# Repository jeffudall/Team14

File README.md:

Welcome to Team 14's Practicum Pages - ECE 411 Fall 2017

This repository will document our practicum project for the ECE 411 Industrial Design course at PSU for Fall 2017. Here you will find details of our project creation as well as documentation detailing the specifications and operation of our final product - a color scanner device.

Team members:

- Matthew Fleetwood fleet@pdx.edu
- Bruce Griffin bruce7@pdx.edu
- Jeffrey Udall judall@pdx.edu
- James Witcher jwitcher@pdx.edu

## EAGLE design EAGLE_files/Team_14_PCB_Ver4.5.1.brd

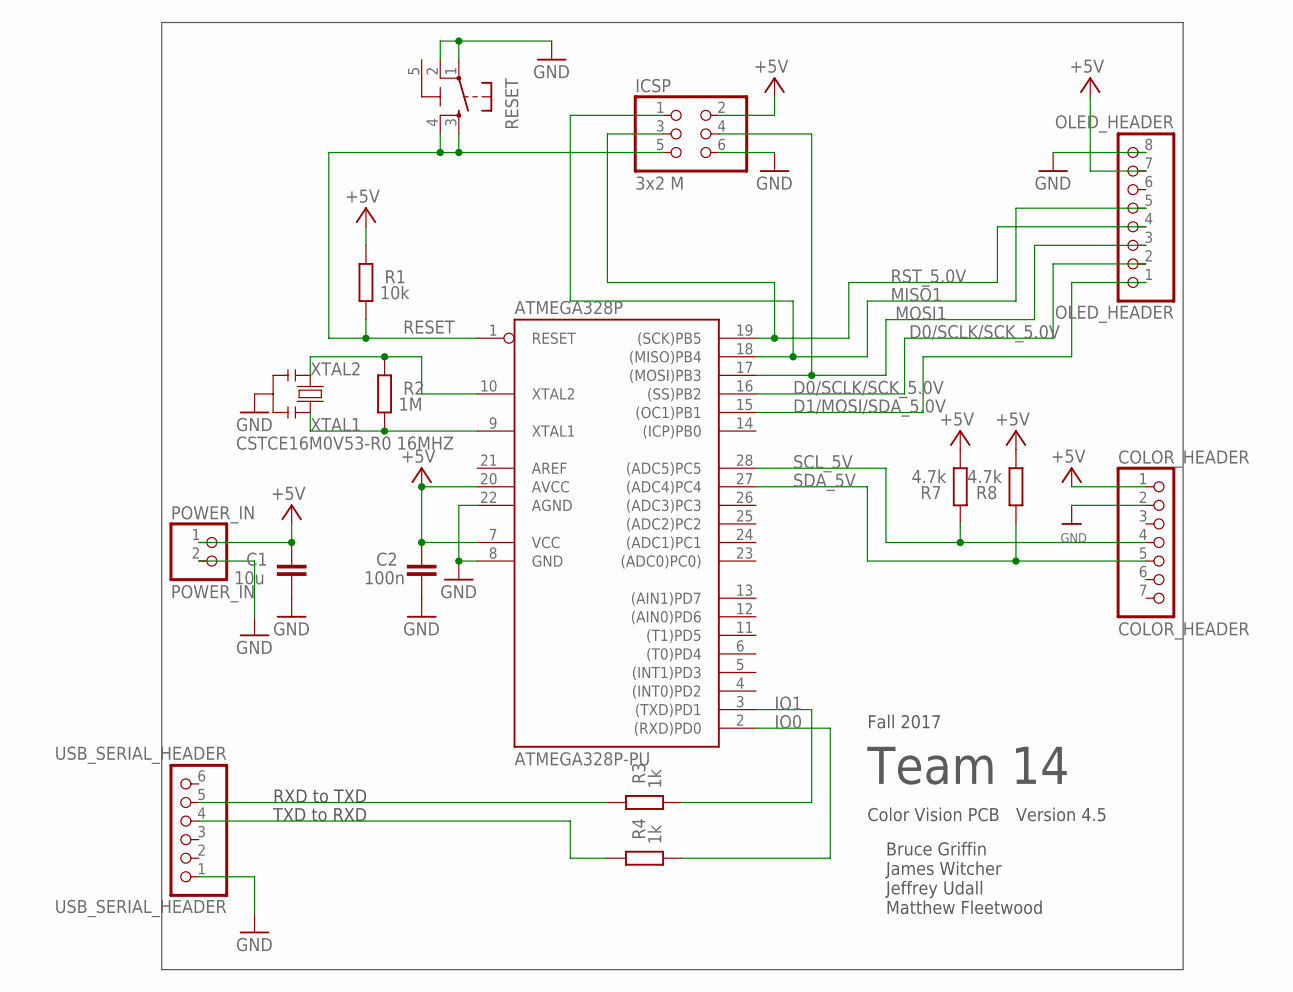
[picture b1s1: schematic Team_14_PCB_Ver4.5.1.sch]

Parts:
ATMEGA328P: ATMEGA328P-PU; DIL28-3
C1: 10u; C0603-ROUND
C2: 100n; C0603-ROUND
COLOR_HEADER: COLOR_HEADER; 1X07_ROUND_70
ICSP: 3x2 M; 2X03
OLED_HEADER: OLED_HEADER; 1X08_ROUND_70
POWER_IN: POWER_IN; 1X02
R1: 10k; R0603-ROUND
R2: 1M; R0603-ROUND
R3, R4: 1k; R0603-ROUND
R7, R8: 4.7k; R0603-ROUND
RESET: TS42
USB_SERIAL_HEADER: USB_SERIAL_HEADER; 1X06
Y2: CSTCE16M0V53-R0 16MHZ; RESONATOR

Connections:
5-GND: RESET.5 (5-GND)
+5V: ATMEGA328P.7 (VCC), ATMEGA328P.20 (AVCC), C1.2, C2.2, COLOR_HEADER.1, ICSP.2, OLED_HEADER.7, POWER_IN.1, R1.2, R7.1, R8.1
D0/SCLK/SCK_5.0V: ATMEGA328P.16 ((SS)PB2), OLED_HEADER.2
D1/MOSI/SDA_5.0V: ATMEGA328P.15 ((OC1)PB1), OLED_HEADER.1
GND: ATMEGA328P.8 (GND), ATMEGA328P.22 (AGND), C1.1, C2.1, COLOR_HEADER.2, ICSP.6, OLED_HEADER.8, POWER_IN.2, RESET.1, RESET.2, USB_SERIAL_HEADER.1, Y2.2
IO0: ATMEGA328P.2 ((RXD)PD0), R4.1
IO1: ATMEGA328P.3 ((TXD)PD1), R3.1
MISO1: ATMEGA328P.18 ((MISO)PB4), ICSP.1, OLED_HEADER.5
MOSI1: ATMEGA328P.17 ((MOSI)PB3), ICSP.4, OLED_HEADER.3
unnamed: R3.2, USB_SERIAL_HEADER.5
unnamed: R4.2, USB_SERIAL_HEADER.4
RESET: ATMEGA328P.1 (RESET), ICSP.5, R1.1, RESET.3, RESET.4
RST_5.0V: ATMEGA328P.19 ((SCK)PB5), ICSP.3, OLED_HEADER.4
SCL_5V: ATMEGA328P.28 ((ADC5)PC5), COLOR_HEADER.4, R7.2
SDA_5V: ATMEGA328P.27 ((ADC4)PC4), COLOR_HEADER.5, R8.2
XTAL1: ATMEGA328P.9 (XTAL1), R2.1, Y2.3
XTAL2: ATMEGA328P.10 (XTAL2), R2.2, Y2.1

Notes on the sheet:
Team 14
Bruce Griffin James Witcher Jeffrey Udall Matthew Fleetwood
Color Vision PCB
Version 4.5
Fall 2017
RXD to TXD
TXD to RXD

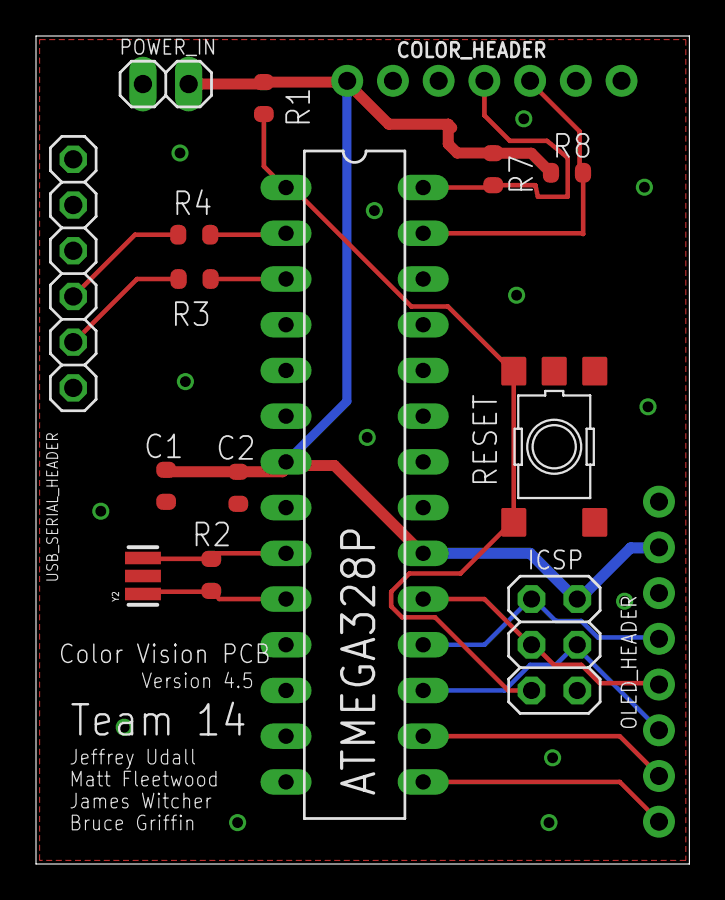
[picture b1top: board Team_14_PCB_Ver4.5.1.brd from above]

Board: 2 copper layers, 36.3 x 46.0 mm, 16 parts (0 on the bottom side), 16 nets.

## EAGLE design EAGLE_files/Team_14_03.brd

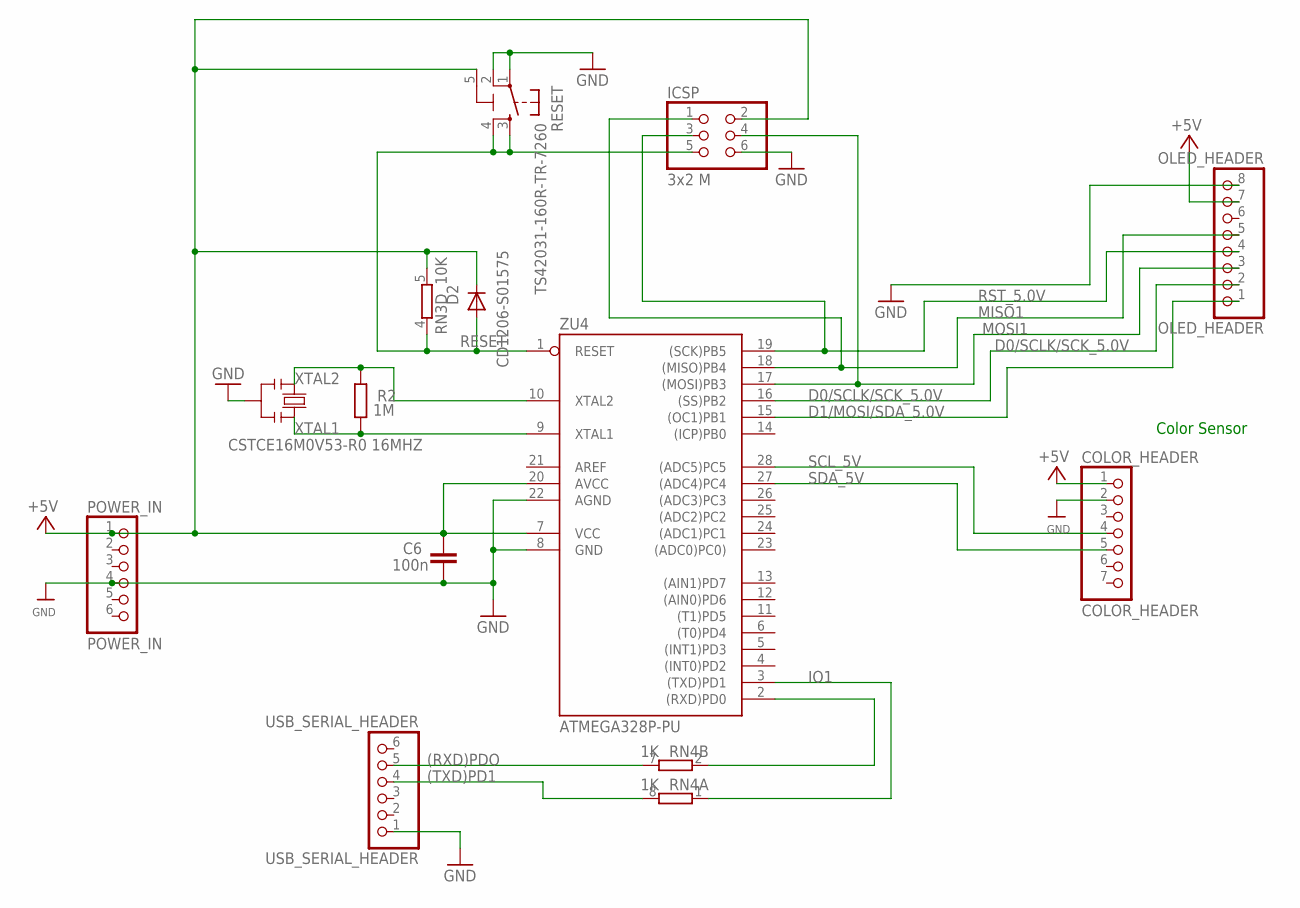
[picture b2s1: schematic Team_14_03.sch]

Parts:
C6: 100n; C0603-ROUND
COLOR_HEADER: COLOR_HEADER; 1X07_ROUND_70
D2: CD1206-S01575; MINIMELF
ICSP: 3x2 M; 2X03
OLED_HEADER: OLED_HEADER; 1X08_ROUND_70
POWER_IN: POWER_IN; 1X06
R2: 1M; R0603-ROUND
RESET: TS42031-160R-TR-7260; TS42
RN3: 10K; CAY16
RN4: 1K; CAY16
USB_SERIAL_HEADER: USB_SERIAL_HEADER; 1X06
Y2: CSTCE16M0V53-R0 16MHZ; RESONATOR
ZU4: ATMEGA328P-PU; DIL28-3

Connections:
(RXD)PDO: RN4.7 (2), USB_SERIAL_HEADER.5
(TXD)PD1: RN4.8 (2), USB_SERIAL_HEADER.4
+5V: C6.2, COLOR_HEADER.1, D2.C, ICSP.2, OLED_HEADER.7, POWER_IN.1, RESET.5 (5-GND), RN3.5 (2), ZU4.7 (VCC), ZU4.20 (AVCC)
D0/SCLK/SCK_5.0V: OLED_HEADER.2, ZU4.16 ((SS)PB2)
D1/MOSI/SDA_5.0V: OLED_HEADER.1, ZU4.15 ((OC1)PB1)
GND: C6.1, COLOR_HEADER.2, ICSP.6, OLED_HEADER.8, POWER_IN.4, RESET.1, RESET.2, USB_SERIAL_HEADER.1, Y2.2, ZU4.8 (GND), ZU4.22 (AGND)
IO1: RN4.1, ZU4.3 ((TXD)PD1)
IO11: RN4.2 (1), ZU4.2 ((RXD)PD0)
MISO1: ICSP.1, OLED_HEADER.5, ZU4.18 ((MISO)PB4)
MOSI1: ICSP.4, OLED_HEADER.3, ZU4.17 ((MOSI)PB3)
RESET: D2.A, ICSP.5, RESET.3, RESET.4, RN3.4 (1), ZU4.1 (RESET)
RST_5.0V: ICSP.3, OLED_HEADER.4, ZU4.19 ((SCK)PB5)
SCL_5V: COLOR_HEADER.4, ZU4.28 ((ADC5)PC5)
SDA_5V: COLOR_HEADER.5, ZU4.27 ((ADC4)PC4)
XTAL1: R2.1, Y2.3, ZU4.9 (XTAL1)
XTAL2: R2.2, Y2.1, ZU4.10 (XTAL2)

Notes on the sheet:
Color Sensor

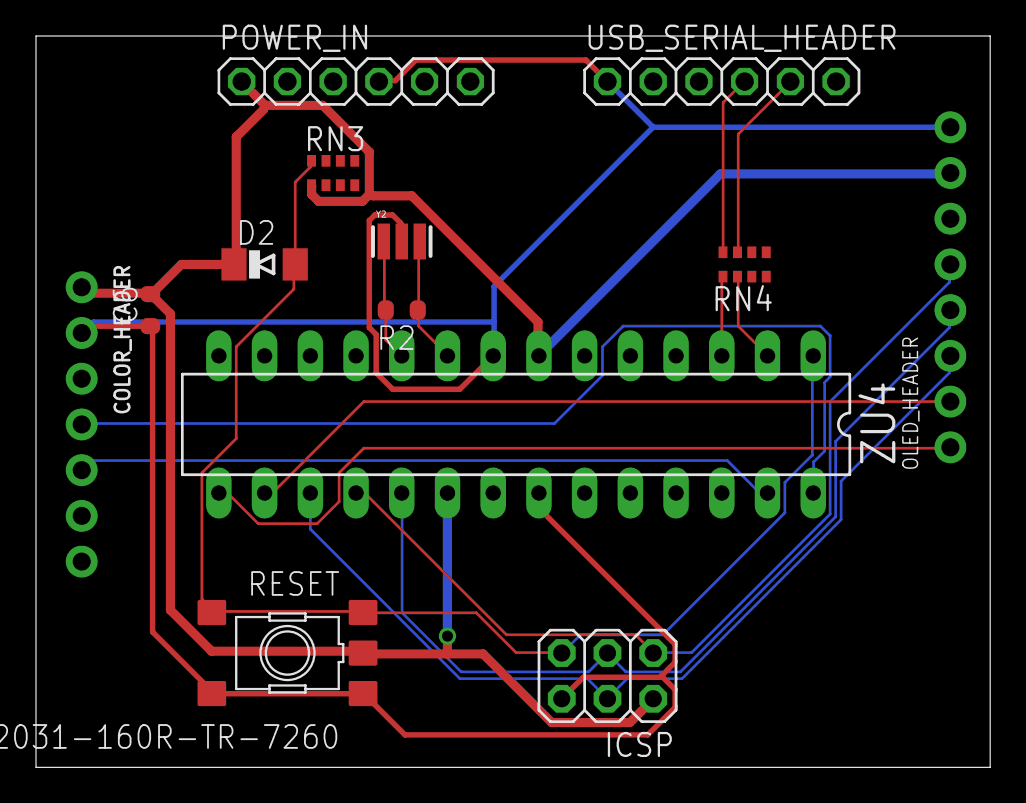
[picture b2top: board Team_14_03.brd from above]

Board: 2 copper layers, 53.0 x 40.6 mm, 13 parts (0 on the bottom side), 16 nets.

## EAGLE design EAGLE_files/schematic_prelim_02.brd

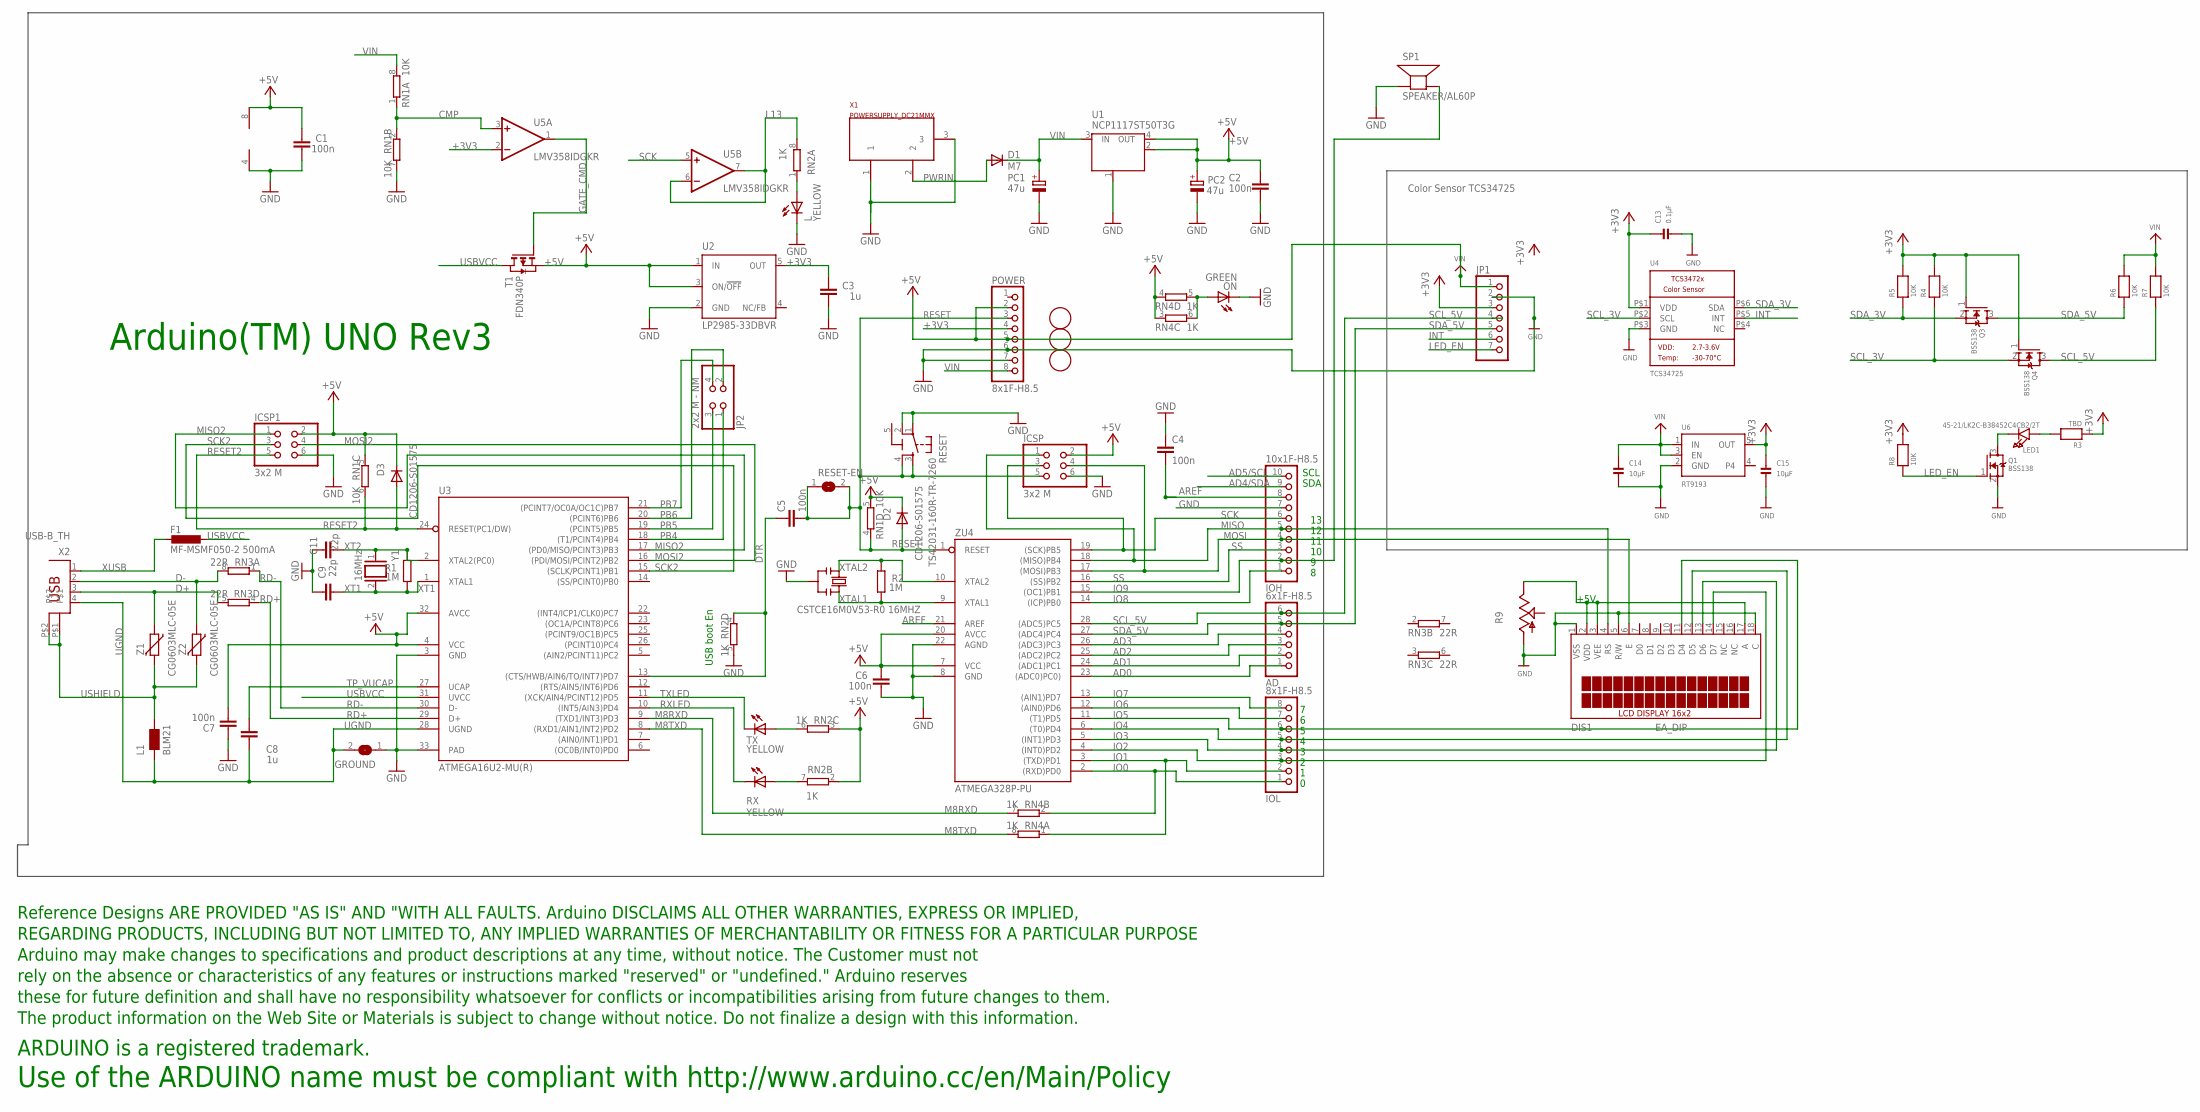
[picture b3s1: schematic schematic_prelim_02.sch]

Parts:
AD: 6x1F-H8.5; 1X06
C1, C2, C4, C5, C6, C7: 100n; C0603-ROUND
C3, C8: 1u; C0603-ROUND
C9, C11: 22p; C0603-ROUND
C13: 0.1µF; _0805
C14, C15: 10µF; _0805
D1: M7; SMB
D2, D3: CD1206-S01575; MINIMELF
DIS1: EA_DIP
F1: MF-MSMF050-2 500mA; L1812
FD1, FD2, FD3: FIDUCIALMOUNT; FIDUCIA-MOUNT
GROUND: SJ
ICSP, ICSP1: 3x2 M; 2X03
IOH: 10x1F-H8.5; 1X10
IOL: 8x1F-H8.5; 1X08
JP1: HEADER-1X770MIL; 1X07_ROUND_70
JP2: 2x2 M - NM; 2X02
L: YELLOW; CHIP-LED0805
L1: BLM21; 0805
LED1: 45-21/LK2C-B38452C4CB2/2T; EVERLIGHT_45-21
ON: GREEN; CHIP-LED0805
PC1, PC2: 47u; PANASONIC_D
POWER: 8x1F-H8.5; 1X08
Q1, Q3, Q4: BSS138; SOT23-WIDE
R1, R2: 1M; R0603-ROUND
R3: TBD; _0805
R4, R5, R6, R7, R8: 10K; _0805
R9: TRIM_US-B25U; B25U
RESET: TS42031-160R-TR-7260; TS42
RESET-EN: SJ
RN1: 10K; CAY16
RN2, RN4: 1K; CAY16
RN3: 22R; CAY16
RX: YELLOW; CHIP-LED0805
SP1: SPEAKER/AL60P; AL60P
T1: FDN340P; SOT-23
TX: YELLOW; CHIP-LED0805
U1: NCP1117ST50T3G; SOT223
U2: LP2985-33DBVR; SOT23-DBV
U3: ATMEGA16U2-MU(R); MLF32
U4: TCS34725; TCS3472_FN6
U5: LMV358IDGKR; MSOP08
U6: RT9193; SOT23-5
U$1: DISCLAIMER
X1: POWERSUPPLY_DC21MMX; POWERSUPPLY_DC-21MM
X2: USB-B_TH; PN61729
Y1: 16MHz; QS
Y2: CSTCE16M0V53-R0 16MHZ; RESONATOR
Z1, Z2: CG0603MLC-05E; CT/CN0603
ZU4: ATMEGA328P-PU; DIL28-3

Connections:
5-GND: RESET.5 (5-GND)
+3V3: C3.2, C13.1, C15.1, JP1.3, POWER.4, Q3.1 (G), Q4.1 (G), R3.1, R4.2, R5.2, R8.2, U2.5 (OUT), U4.P$1 (VDD), U5.2 (-IN), U6.5 (OUT)
+5V: C1.2, C2.2, C6.2, C7.1, D2.C, D3.C, ICSP.2, ICSP1.2, JP1.1, PC2.+, POWER.2, POWER.5, RN1.3 (1), RN1.5 (2), RN2.2 (1), RN2.3 (1), RN4.3 (1), RN4.4 (1), T1.2 (S), U1.2 (OUT), U1.4 (OUT), U2.1 (IN), U2.3 (ON/!OFF), U3.4 (VCC), U3.32 (AVCC), U5.8 (V+), ZU4.7 (VCC), ZU4.20 (AVCC)
AD0: AD.1, ZU4.23 ((ADC0)PC0))
AD1: AD.2, ZU4.24 ((ADC1)PC1)
AD2: AD.3, ZU4.25 ((ADC2)PC2)
AD3: AD.4, ZU4.26 ((ADC3)PC3)
AD4/SDA: IOH.9
AD5/SCL: IOH.10
AREF: C4.2, IOH.8, ZU4.21 (AREF)
CMP: RN1.1, RN1.2 (1), U5.3 (+IN)
D+: RN3.5 (2), X2.3, Z1.1
D-: RN3.8 (2), X2.2, Z2.1
DTR: C5.1, RN2.4 (1), U3.13 ((CTS/HWB/AIN6/TO/INT7)PD7)
GATE_CMD: T1.3 (G), U5.1 (OUT)
GND: C1.1, C2.1, C3.1, C4.1, C6.1, C7.2, C9.2, C11.2, C13.2, C14.2, C15.2, DIS1.1 (VSS), DIS1.5 (R/W), DIS1.18 (C), GROUND.1, ICSP.6, ICSP1.6, IOH.7, JP1.2, L.C, ON.C, PC1.-, PC2.-, POWER.6, POWER.7, Q1.2 (S), R9.A, RESET.1, RESET.2, RN1.7 (2), RN2.5 (2), SP1.1 (+), U1.1 (GND/ADJ), U2.2 (GND), U3.3 (GND), U3.33 (PAD), U4.P$3 (GND), U5.4 (V-), U6.2 (GND), X1.1, X1.3, Y2.2, ZU4.8 (GND), ZU4.22 (AGND)
INT: JP1.6, U4.P$5 (INT)
IO0: IOL.1, RN4.2 (1), ZU4.2 ((RXD)PD0)
IO1: IOL.2, RN4.1, ZU4.3 ((TXD)PD1)
IO2: DIS1.14 (D7), IOL.3, ZU4.4 ((INT0)PD2)
IO3: DIS1.13 (D6), IOL.4, ZU4.5 ((INT1)PD3)
IO4: DIS1.12 (D5), IOL.5, ZU4.6 ((T0)PD4)
IO5: DIS1.11 (D4), IOL.6, ZU4.11 ((T1)PD5)
IO6: IOL.7, ZU4.12 ((AIN0)PD6)
IO7: IOL.8, ZU4.13 ((AIN1)PD7)
IO8: IOH.1, ZU4.14 ((ICP)PB0)
IO9: IOH.2, SP1.2 (-), ZU4.15 ((OC1)PB1)
L13: RN2.8 (2), U5.6 (-IN), U5.7 (OUT)
LED_EN: JP1.7, Q1.1 (G), R8.1
M8RXD: RN4.7 (2), U3.9 ((TXD1/INT3)PD3)
M8TXD: RN4.8 (2), U3.8 ((RXD1/AIN1/INT2)PD2)
MISO: DIS1.4 (RS), ICSP.1, IOH.5, ZU4.18 ((MISO)PB4)
MISO2: ICSP1.1, U3.17 ((PD0/MISO/PCINT3)PB3)
MOSI: DIS1.6 (E), ICSP.4, IOH.4, ZU4.17 ((MOSI)PB3)
MOSI2: ICSP1.4, U3.16 ((PDI/MOSI/PCINT2)PB2)
unnamed: L.A, RN2.1
unnamed: LED1.K (C), Q1.3 (D)
unnamed: ON.A, RN4.5 (2), RN4.6 (2)
unnamed: LED1.A, R3.2
unnamed: DIS1.2 (VDD), DIS1.3 (VEE), DIS1.17 (A), R9.E
unnamed: RN2.7 (2), RX.A
unnamed: RN2.6 (2), TX.A
PB4: JP2.1, U3.18 ((T1/PCINT4)PB4)
PB5: JP2.3, U3.19 ((PCINT5)PB5)
PB6: JP2.2, U3.20 ((PCINT6)PB6)
PB7: JP2.4, U3.21 ((PCINT7/OC0A/OC1C)PB7)
PWRIN: D1.A, X1.2
RD+: RN3.4 (1), U3.29 (D+)
RD-: RN3.1, U3.30 (D-)
RESET: C5.2, D2.A, ICSP.5, POWER.3, RESET.3, RESET.4, RESET-EN.1, RESET-EN.2, RN1.4 (1), ZU4.1 (RESET)
RESET2: D3.A, ICSP1.5, RN1.6 (2), U3.24 (RESET(PC1/DW))
RXLED: RX.C, U3.10 ((INT5/AIN3)PD4)
SCK: ICSP.3, IOH.6, U5.5 (+IN), ZU4.19 ((SCK)PB5)
SCK2: ICSP1.3, U3.15 ((SCLK/PCINT1)PB1)
SCL_3V: Q4.2 (S), R4.1, U4.P$2 (SCL)
SCL_5V: AD.6, JP1.4, Q4.3 (D), R7.1, ZU4.28 ((ADC5)PC5)
SDA_3V: Q3.2 (S), R5.1, U4.P$6 (SDA)
SDA_5V: AD.5, JP1.5, Q3.3 (D), R6.1, ZU4.27 ((ADC4)PC4)
SS: IOH.3, ZU4.16 ((SS)PB2)
TP_VUCAP: C8.1, U3.27 (UCAP)
TXLED: TX.C, U3.11 ((XCK/AIN4/PCINT12)PD5)
UGND: C8.2, GROUND.2, L1.1, U3.28 (UGND), X2.4
USBVCC: F1.1, T1.1 (D), U3.31 (UVCC)
USHIELD: L1.2, X2.P$1, X2.P$2, Z1.2, Z2.2
VIN: C14.1, D1.C, PC1.+, POWER.8, R6.2, R7.2, RN1.8 (2), U1.3 (IN), U6.1 (IN), U6.3 (EN)
XT1: C9.1, R1.1, U3.1 (XTAL1), Y1.2
XT2: C11.1, R1.2, U3.2 (XTAL2(PC0)), Y1.1
XTAL1: R2.1, Y2.3, ZU4.9 (XTAL1)
XTAL2: R2.2, Y2.1, ZU4.10 (XTAL2)
XUSB: F1.2, X2.1

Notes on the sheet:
Arduino(TM) UNO Rev3
USB boot En
SDA
SCL
Use of the ARDUINO name must be compliant with http://www.arduino.cc/en/Main/Policy
Color Sensor TCS34725
+5V

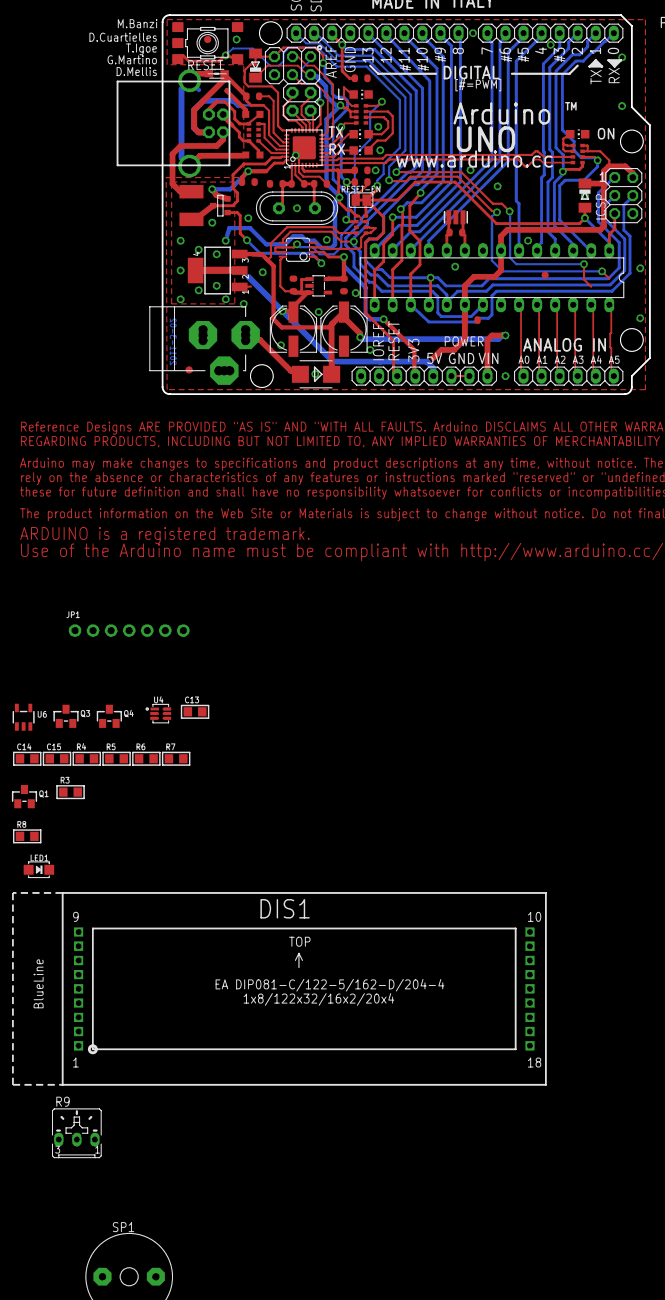
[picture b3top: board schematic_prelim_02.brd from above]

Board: 2 copper layers, 68.6 x 53.3 mm, 72 parts (1 on the bottom side), 67 nets.

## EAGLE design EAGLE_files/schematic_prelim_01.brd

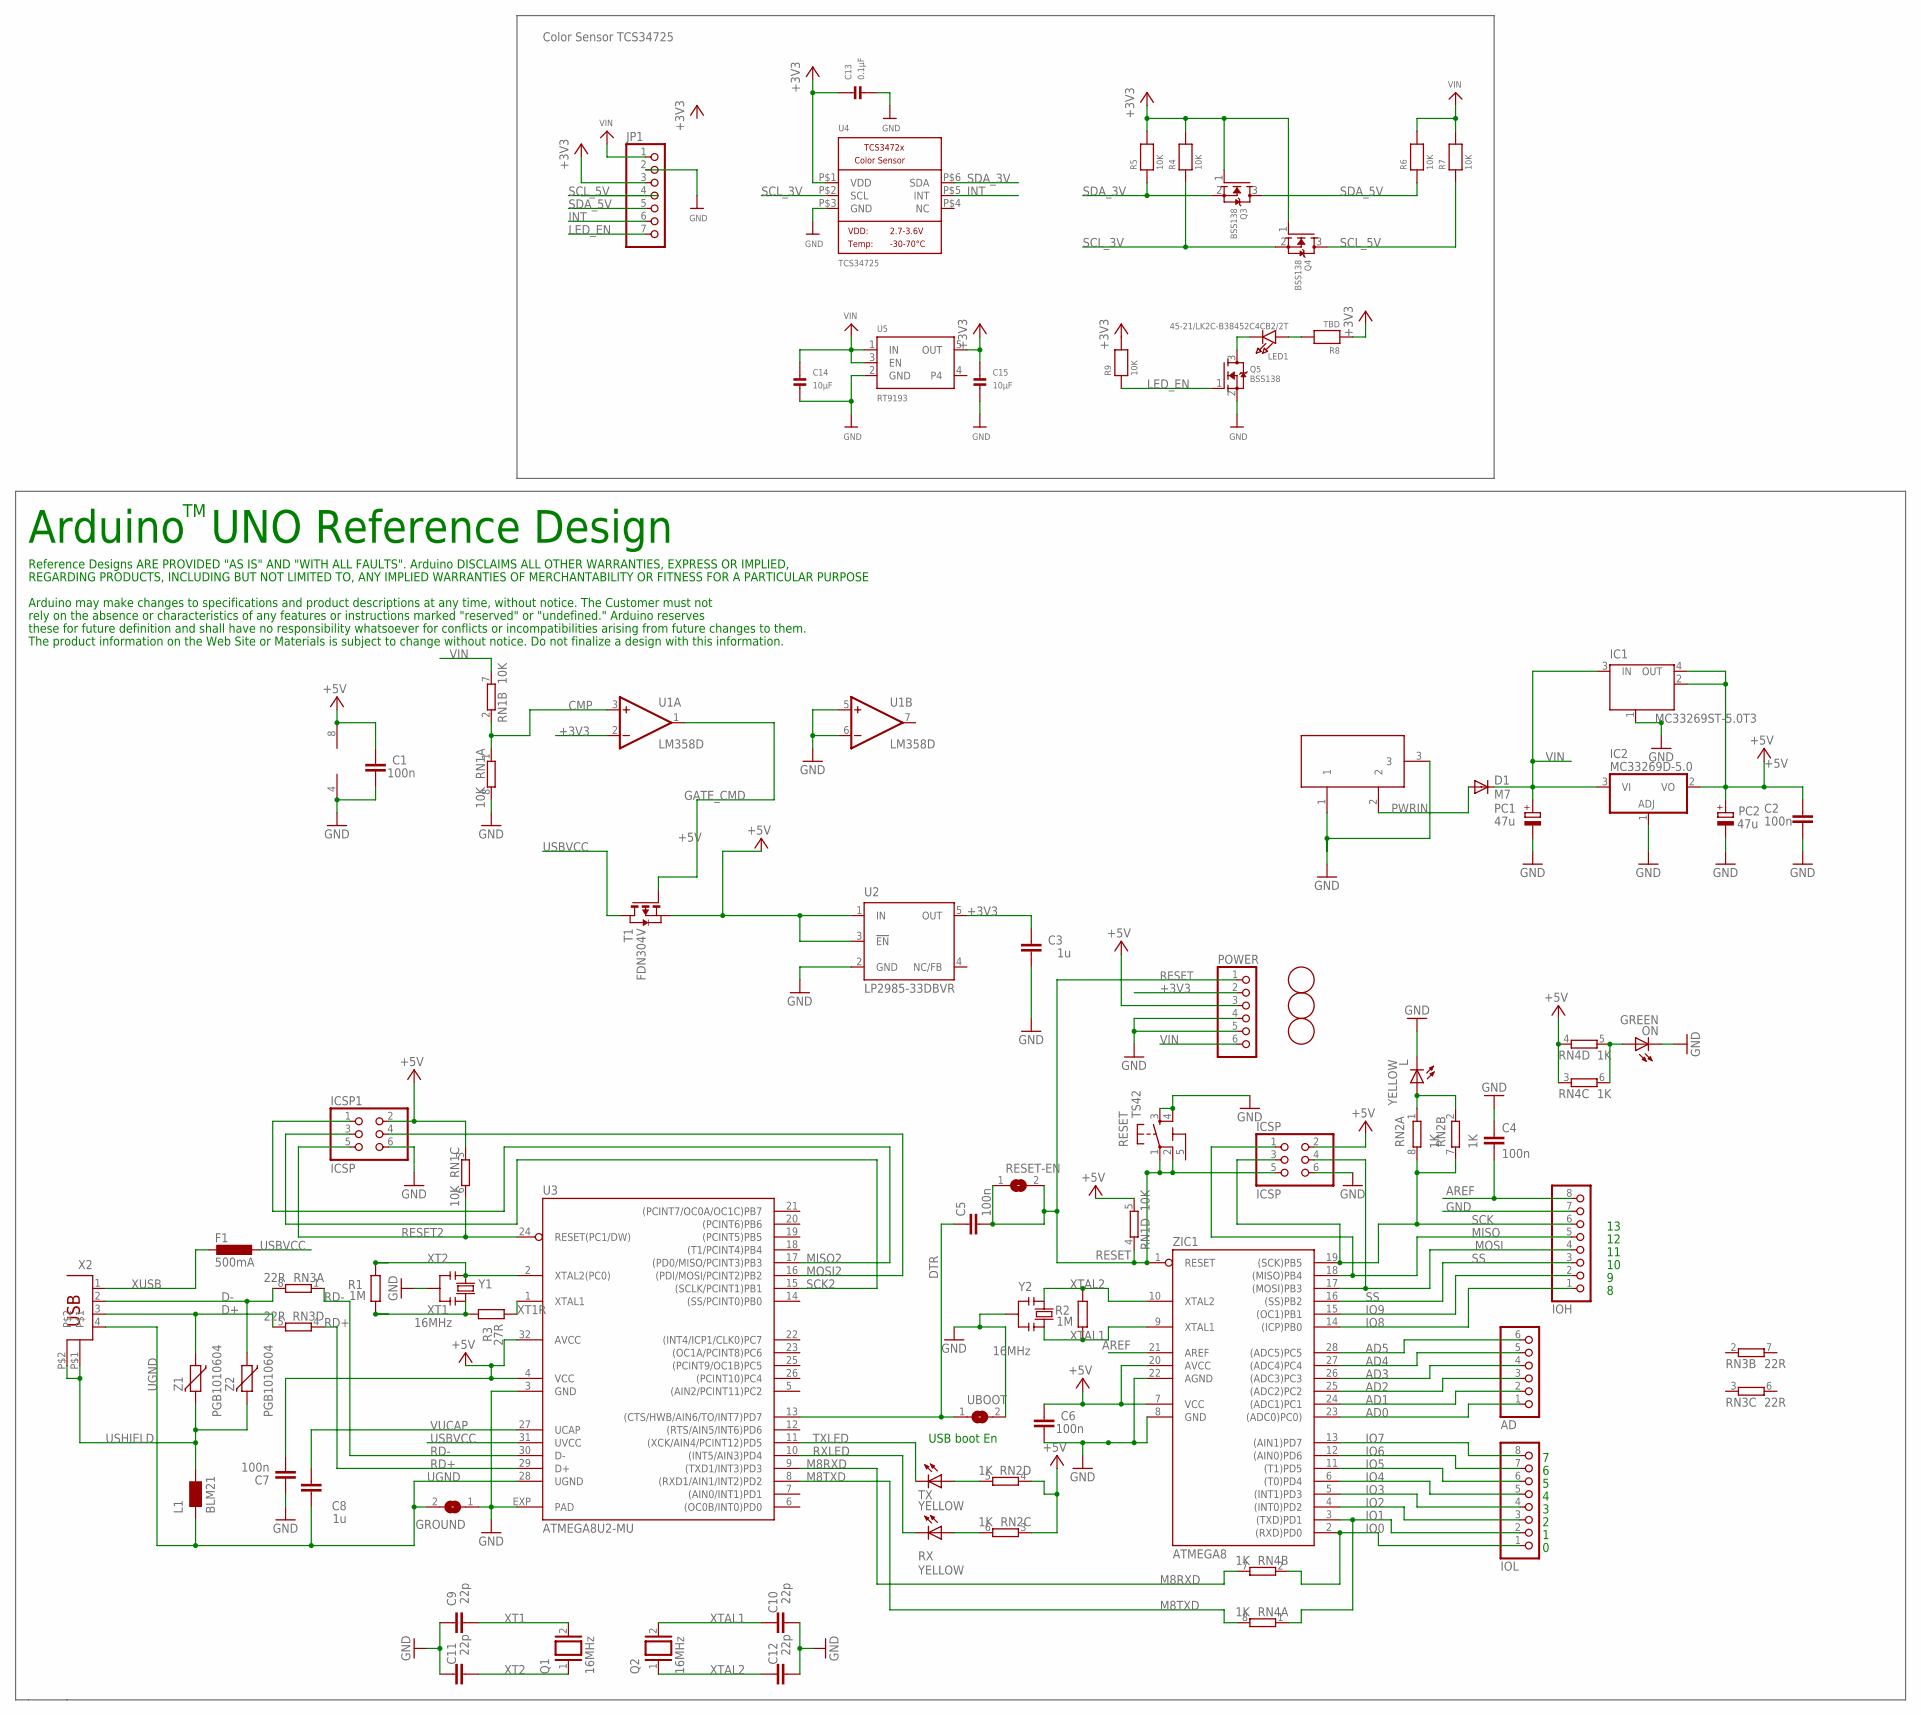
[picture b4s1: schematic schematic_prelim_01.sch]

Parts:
AD: PINHD-1X6; 1X06
C1, C2, C4, C5, C6, C7: 100n; C0603-ROUND
C3, C8: 1u; C0603-ROUND
C9, C10, C11, C12: 22p; C0603-ROUND
C13: 0.1µF; _0805
C14, C15: 10µF; _0805
D1: M7; SMB
F1: 500mA; L1812
GROUND: SJ
IC1: MC33269ST-5.0T3; SOT223
IC2: MC33269D-5.0; DPACK
ICSP, ICSP1: ICSP; 2X03
IOH: PINHD-1X8; 1X08
IOL: PINHD-1X8; 1X08
JP1: HEADER-1X770MIL; 1X07_ROUND_70
L: YELLOW; CHIP-LED0805
L1: BLM21; 0805
LED1: 45-21/LK2C-B38452C4CB2/2T; EVERLIGHT_45-21
ON: GREEN; CHIP-LED0805
PC1, PC2: 47u; PANASONIC_D
POWER: PINHD-1X6; 1X06
Q1, Q2: 16MHz; QS
Q3, Q4, Q5: BSS138; SOT23-WIDE
R1, R2: 1M; R0603-ROUND
R3: 27R; R0603-ROUND
R4, R5, R6, R7, R9: 10K; _0805
R8: TBD; _0805
RESET: TS42
RESET-EN: SJ
RN1: 10K; CAY16
RN2, RN4: 1K; CAY16
RN3: 22R; CAY16
RX: YELLOW; CHIP-LED0805
T1: FDN304V; SOT-23
TX: YELLOW; CHIP-LED0805
U1: LM358D; SO08
U2: LP2985-33DBVR; SOT23-DBV
U3: ATMEGA8U2-MU; QFN32
U4: TCS34725; TCS3472_FN6
U5: RT9193; SOT23-5
U$3, U$4, U$6: FIDUCIALMOUNT; FIDUCIA-MOUNT
UBOOT: SJ
X1: DC21MMX; DC-21MM
X2: PN61729
Y1, Y2: 16MHz; RESONATOR
Z1, Z2: PGB1010604; CT/CN0603
ZIC1: ATMEGA8; DIL28-3

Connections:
5-GND: RESET.5 (5-GND)
+3V3: C3.2, C13.1, C15.1, JP1.3, POWER.2, Q3.1 (G), Q4.1 (G), R4.2, R5.2, R8.1, R9.2, U1.2 (-IN), U2.5 (OUT), U4.P$1 (VDD), U5.5 (OUT)
+5V: C1.2, C2.2, C6.2, C7.1, IC1.2 (OUT), IC1.4 (OUT), IC2.2 (VO), ICSP.2, ICSP1.2, PC2.+, POWER.3, RN1.3 (1), RN1.5 (2), RN2.3 (1), RN2.4 (1), RN4.3 (1), RN4.4 (1), T1.2 (S), U1.8 (V+), U2.1 (IN), U2.3 (!EN), U3.4 (VCC), U3.32 (AVCC), ZIC1.7 (VCC), ZIC1.20 (AVCC)
AD0: AD.1, ZIC1.23 ((ADC0)PC0))
AD1: AD.2, ZIC1.24 ((ADC1)PC1)
AD2: AD.3, ZIC1.25 ((ADC2)PC2)
AD3: AD.4, ZIC1.26 ((ADC3)PC3)
AD4: AD.5, ZIC1.27 ((ADC4)PC4)
AD5: AD.6, ZIC1.28 ((ADC5)PC5)
AREF: C4.2, IOH.8, ZIC1.21 (AREF)
CMP: RN1.1, RN1.2 (1), U1.3 (+IN)
D+: RN3.5 (2), X2.3, Z1.1
D-: RN3.8 (2), X2.2, Z2.1
DTR: C5.1, U3.13 ((CTS/HWB/AIN6/TO/INT7)PD7), UBOOT.1
GATE_CMD: T1.3 (G), U1.1 (OUT)
GND: C1.1, C2.1, C3.1, C4.1, C6.1, C7.2, C9.2, C10.1, C11.2, C12.1, C13.2, C14.2, C15.2, GROUND.1, IC1.1 (GND/ADJ), IC2.1 (ADJ), ICSP.6, ICSP1.6, IOH.7, JP1.2, L.C, ON.C, PC1.-, PC2.-, POWER.4, POWER.5, Q5.2 (S), RESET.3, RESET.4, RN1.8 (2), U1.4 (V-), U1.5 (+IN), U1.6 (-IN), U2.2 (GND), U3.3 (GND), U3.EXP (PAD), U4.P$3 (GND), U5.2 (GND), UBOOT.2, X1.1, X1.3, Y1.2, Y2.2, ZIC1.8 (GND), ZIC1.22 (AGND)
INT: JP1.6, U4.P$5 (INT)
IO0: IOL.1, RN4.2 (1), ZIC1.2 ((RXD)PD0)
IO1: IOL.2, RN4.1, ZIC1.3 ((TXD)PD1)
IO2: IOL.3, ZIC1.4 ((INT0)PD2)
IO3: IOL.4, ZIC1.5 ((INT1)PD3)
IO4: IOL.5, ZIC1.6 ((T0)PD4)
IO5: IOL.6, ZIC1.11 ((T1)PD5)
IO6: IOL.7, ZIC1.12 ((AIN0)PD6)
IO7: IOL.8, ZIC1.13 ((AIN1)PD7)
IO8: IOH.1, ZIC1.14 ((ICP)PB0)
IO9: IOH.2, ZIC1.15 ((OC1)PB1)
LED_EN: JP1.7, Q5.1 (G), R9.1
M8RXD: RN4.7 (2), U3.9 ((TXD1/INT3)PD3)
M8TXD: RN4.8 (2), U3.8 ((RXD1/AIN1/INT2)PD2)
MISO: ICSP.1, IOH.5, ZIC1.18 ((MISO)PB4)
MISO2: ICSP1.1, U3.17 ((PD0/MISO/PCINT3)PB3)
MOSI: ICSP.4, IOH.4, ZIC1.17 ((MOSI)PB3)
MOSI2: ICSP1.4, U3.16 ((PDI/MOSI/PCINT2)PB2)
unnamed: LED1.K (C), Q5.3 (D)
unnamed: L.A, RN2.1, RN2.2 (1)
unnamed: ON.A, RN4.5 (2), RN4.6 (2)
unnamed: LED1.A, R8.2
unnamed: RN2.6 (2), RX.A
unnamed: RN2.5 (2), TX.A
PWRIN: D1.A, X1.2
RD+: RN3.4 (1), U3.29 (D+)
RD-: RN3.1, U3.30 (D-)
RESET: C5.2, ICSP.5, POWER.1, RESET.1, RESET.2, RESET-EN.1, RESET-EN.2, RN1.4 (1), ZIC1.1 (RESET)
RESET2: ICSP1.5, RN1.6 (2), U3.24 (RESET(PC1/DW))
RXLED: RX.C, U3.10 ((INT5/AIN3)PD4)
SCK: ICSP.3, IOH.6, RN2.7 (2), RN2.8 (2), ZIC1.19 ((SCK)PB5)
SCK2: ICSP1.3, U3.15 ((SCLK/PCINT1)PB1)
SCL_3V: Q4.2 (S), R4.1, U4.P$2 (SCL)
SCL_5V: JP1.4, Q4.3 (D), R7.1
SDA_3V: Q3.2 (S), R5.1, U4.P$6 (SDA)
SDA_5V: JP1.5, Q3.3 (D), R6.1
SS: IOH.3, ZIC1.16 ((SS)PB2)
TXLED: TX.C, U3.11 ((XCK/AIN4/PCINT12)PD5)
UGND: C8.2, GROUND.2, L1.1, U3.28 (UGND), X2.4
USBVCC: F1.1, T1.1 (D), U3.31 (UVCC)
USHIELD: L1.2, X2.P$1, X2.P$2, Z1.2, Z2.2
VIN: C14.1, D1.C, IC1.3 (IN), IC2.3 (VI), JP1.1, PC1.+, POWER.6, R6.2, R7.2, RN1.7 (2), U5.1 (IN), U5.3 (EN)
VUCAP: C8.1, U3.27 (UCAP)
XT1: C9.1, Q1.2, R1.1, R3.2, Y1.3
XT1R: R3.1, U3.1 (XTAL1)
XT2: C11.1, Q1.1, R1.2, U3.2 (XTAL2(PC0)), Y1.1
XTAL1: C10.2, Q2.2, R2.1, Y2.3, ZIC1.9 (XTAL1)
XTAL2: C12.2, Q2.1, R2.2, Y2.1, ZIC1.10 (XTAL2)
XUSB: F1.2, X2.1

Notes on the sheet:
Arduino UNO Reference Design
USB boot En
Reference Designs ARE PROVIDED "AS IS" AND "WITH ALL FAULTS". Arduino DISCLAIMS ALL OTHER WARRANTIES, EXPRESS OR IMPLIED,
Arduino may make changes to specifications and product descriptions at any time, without notice. The Customer must not
REGARDING PRODUCTS, INCLUDING BUT NOT LIMITED TO, ANY IMPLIED WARRANTIES OF MERCHANTABILITY OR FITNESS FOR A PARTICULAR PURPOSE
rely on the absence or characteristics of any features or instructions marked "reserved" or "undefined." Arduino reserves
these for future definition and shall have no responsibility whatsoever for conflicts or incompatibilities arising from future changes to them.
The product information on the Web Site or Materials is subject to change without notice. Do not finalize a design with this information.
Color Sensor TCS34725

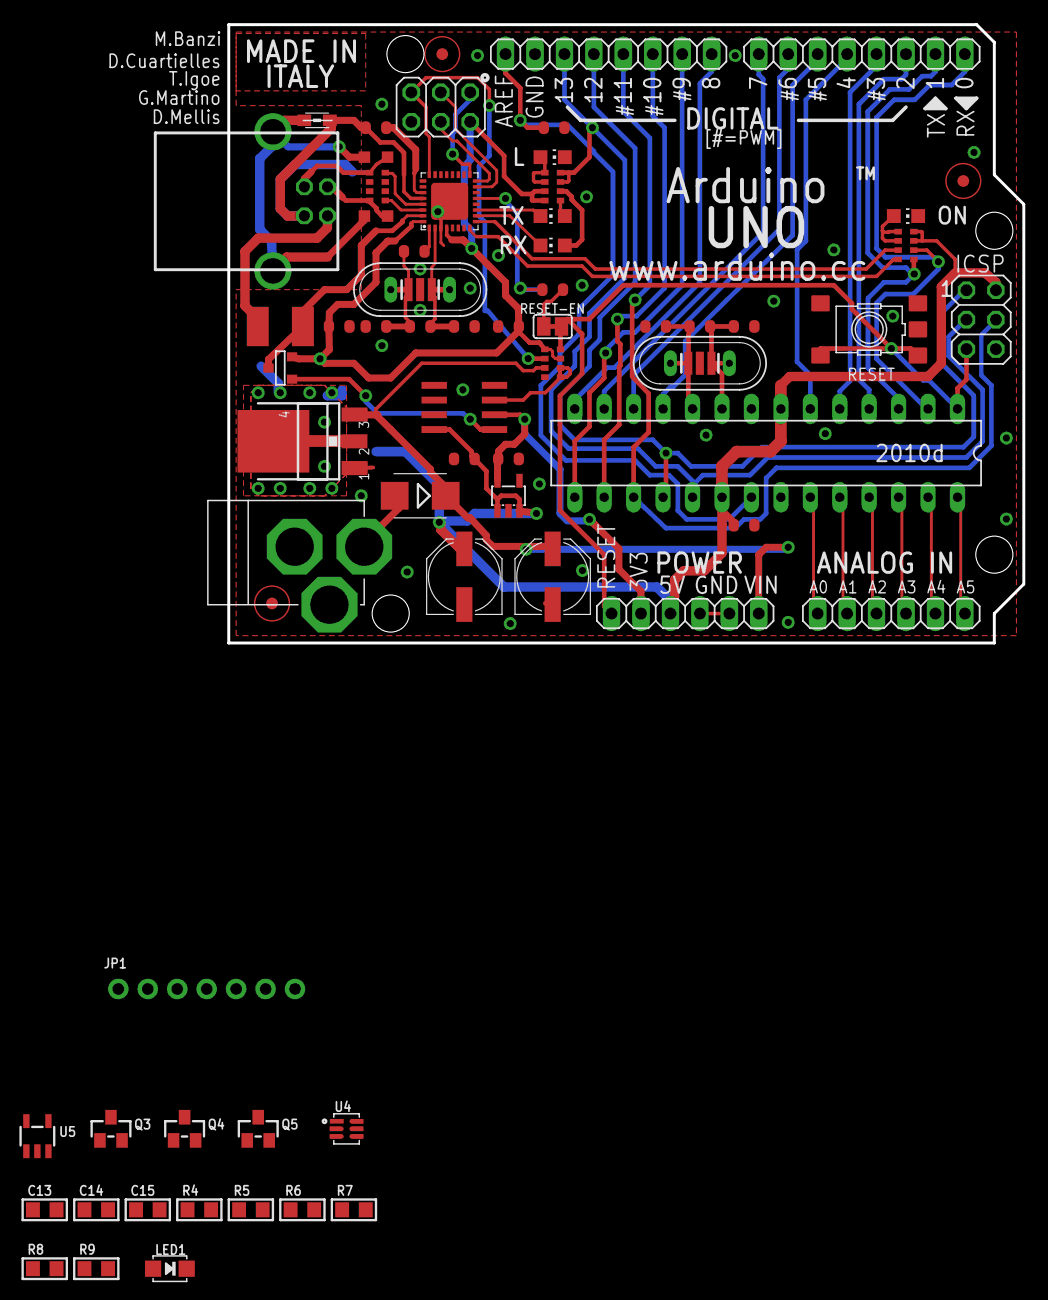
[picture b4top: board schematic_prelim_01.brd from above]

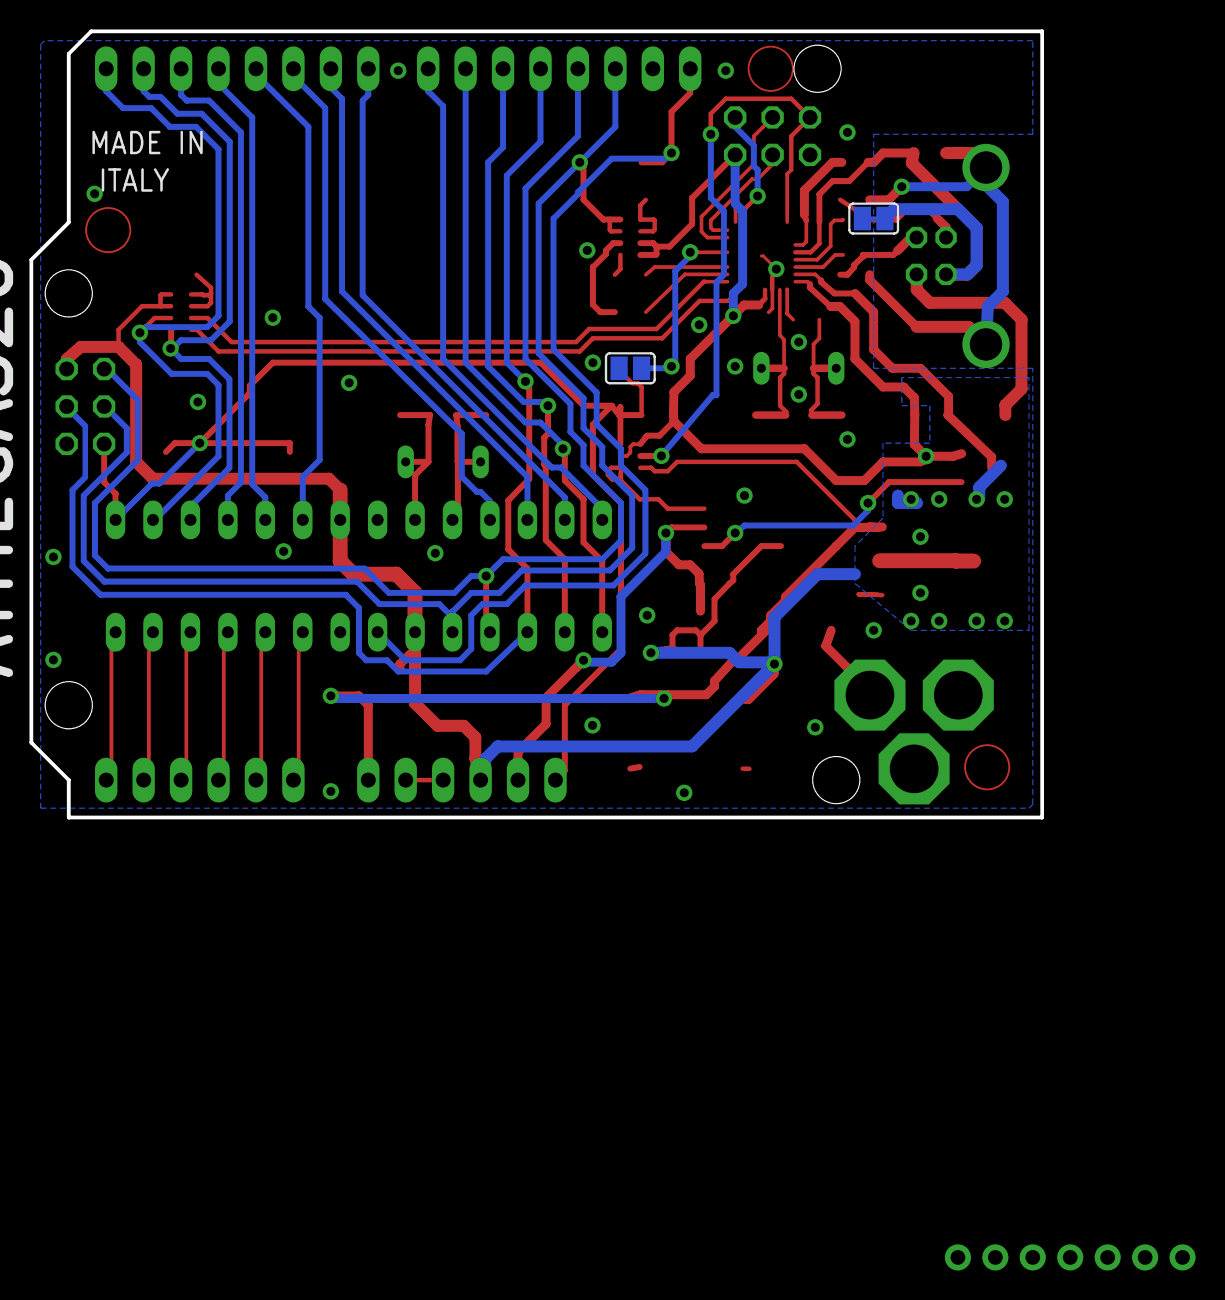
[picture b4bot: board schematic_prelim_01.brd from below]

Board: 2 copper layers, 68.6 x 53.3 mm, 72 parts (2 on the bottom side), 64 nets.

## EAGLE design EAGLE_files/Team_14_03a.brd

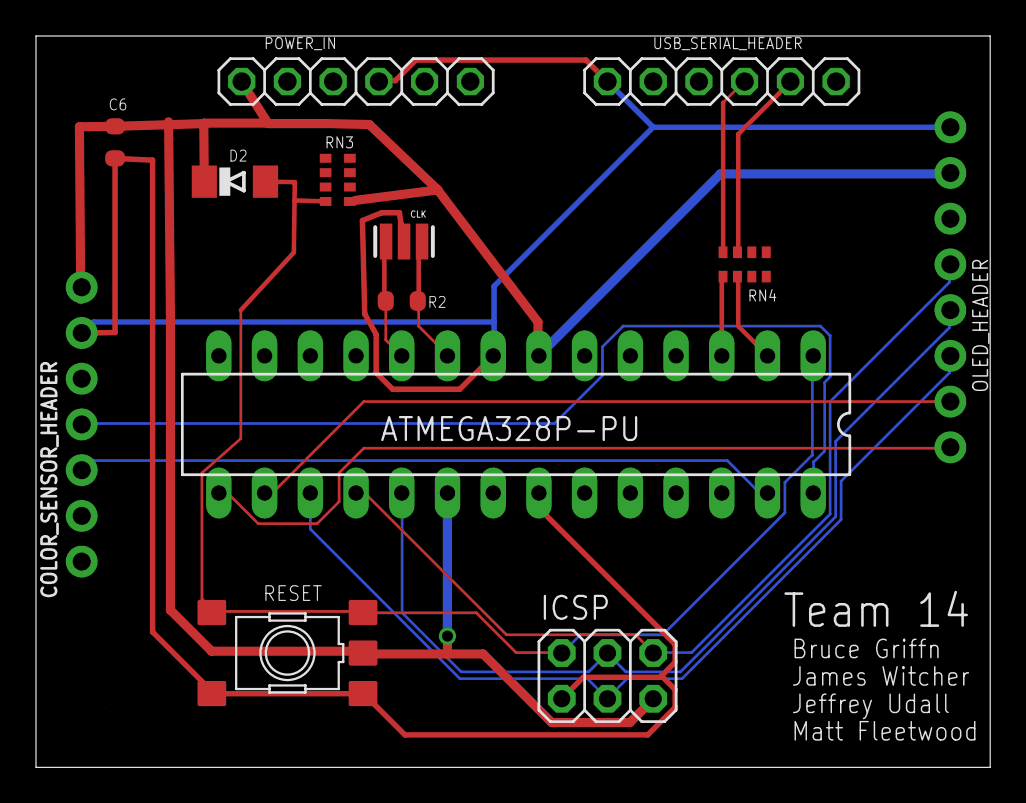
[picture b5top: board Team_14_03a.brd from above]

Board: 2 copper layers, 53.0 x 40.6 mm, 13 parts (0 on the bottom side), 19 nets.

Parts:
ATMEGA328P-PU: DIL28-3
C6: 100n; C0603-ROUND
CLK: CSTCE16M0V53-R0 16MHZ; RESONATOR
COLOR_SENSOR_HEADER: 1X07_ROUND_70
D2: CD1206-S01575; MINIMELF
ICSP: 2X03
OLED_HEADER: 1X08_ROUND_70
POWER_IN: 1X06
R2: 1M; R0603-ROUND
RESET: TS42
RN3: 10K; CAY16
RN4: 1K; CAY16
USB_SERIAL_HEADER: 1X06

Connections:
(RXD)PDO: RN4.7, USB_SERIAL_HEADER.5
(TXD)PD1: RN4.8, USB_SERIAL_HEADER.4
+5V: ATMEGA328P-PU.20, ICSP.2, RESET.5
D0/SCLK/SCK_5.0V: ATMEGA328P-PU.16, OLED_HEADER.2
D1/MOSI/SDA_5.0V: ATMEGA328P-PU.15, OLED_HEADER.1
GND: ATMEGA328P-PU.8, ATMEGA328P-PU.22, C6.1, CLK.2, COLOR_SENSOR_HEADER.2, ICSP.6, OLED_HEADER.8, POWER_IN.4, RESET.1, RESET.2, USB_SERIAL_HEADER.1
IO1: ATMEGA328P-PU.3, RN4.1
IO11: ATMEGA328P-PU.2, RN4.2
MISO1: ATMEGA328P-PU.18, ICSP.1, OLED_HEADER.5
MOSI1: ATMEGA328P-PU.17, ICSP.4, OLED_HEADER.3
RESET: ATMEGA328P-PU.1, D2.A, ICSP.5, RESET.3, RESET.4
RST_5.0V: ATMEGA328P-PU.19, ICSP.3, OLED_HEADER.4
S$1: ATMEGA328P-PU.7, OLED_HEADER.7
S$2: C6.2, COLOR_SENSOR_HEADER.1
S$5: D2.C, POWER_IN.1
SCL_5V: ATMEGA328P-PU.28, COLOR_SENSOR_HEADER.4
SDA_5V: ATMEGA328P-PU.27, COLOR_SENSOR_HEADER.5
XTAL1: ATMEGA328P-PU.9, CLK.3, R2.1
XTAL2: ATMEGA328P-PU.10, CLK.1, R2.2

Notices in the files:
parts and their libraries:
microbuilder: This work is placed in the public domain, and may be freely used for commercial and non-commercial work with the following conditions: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
